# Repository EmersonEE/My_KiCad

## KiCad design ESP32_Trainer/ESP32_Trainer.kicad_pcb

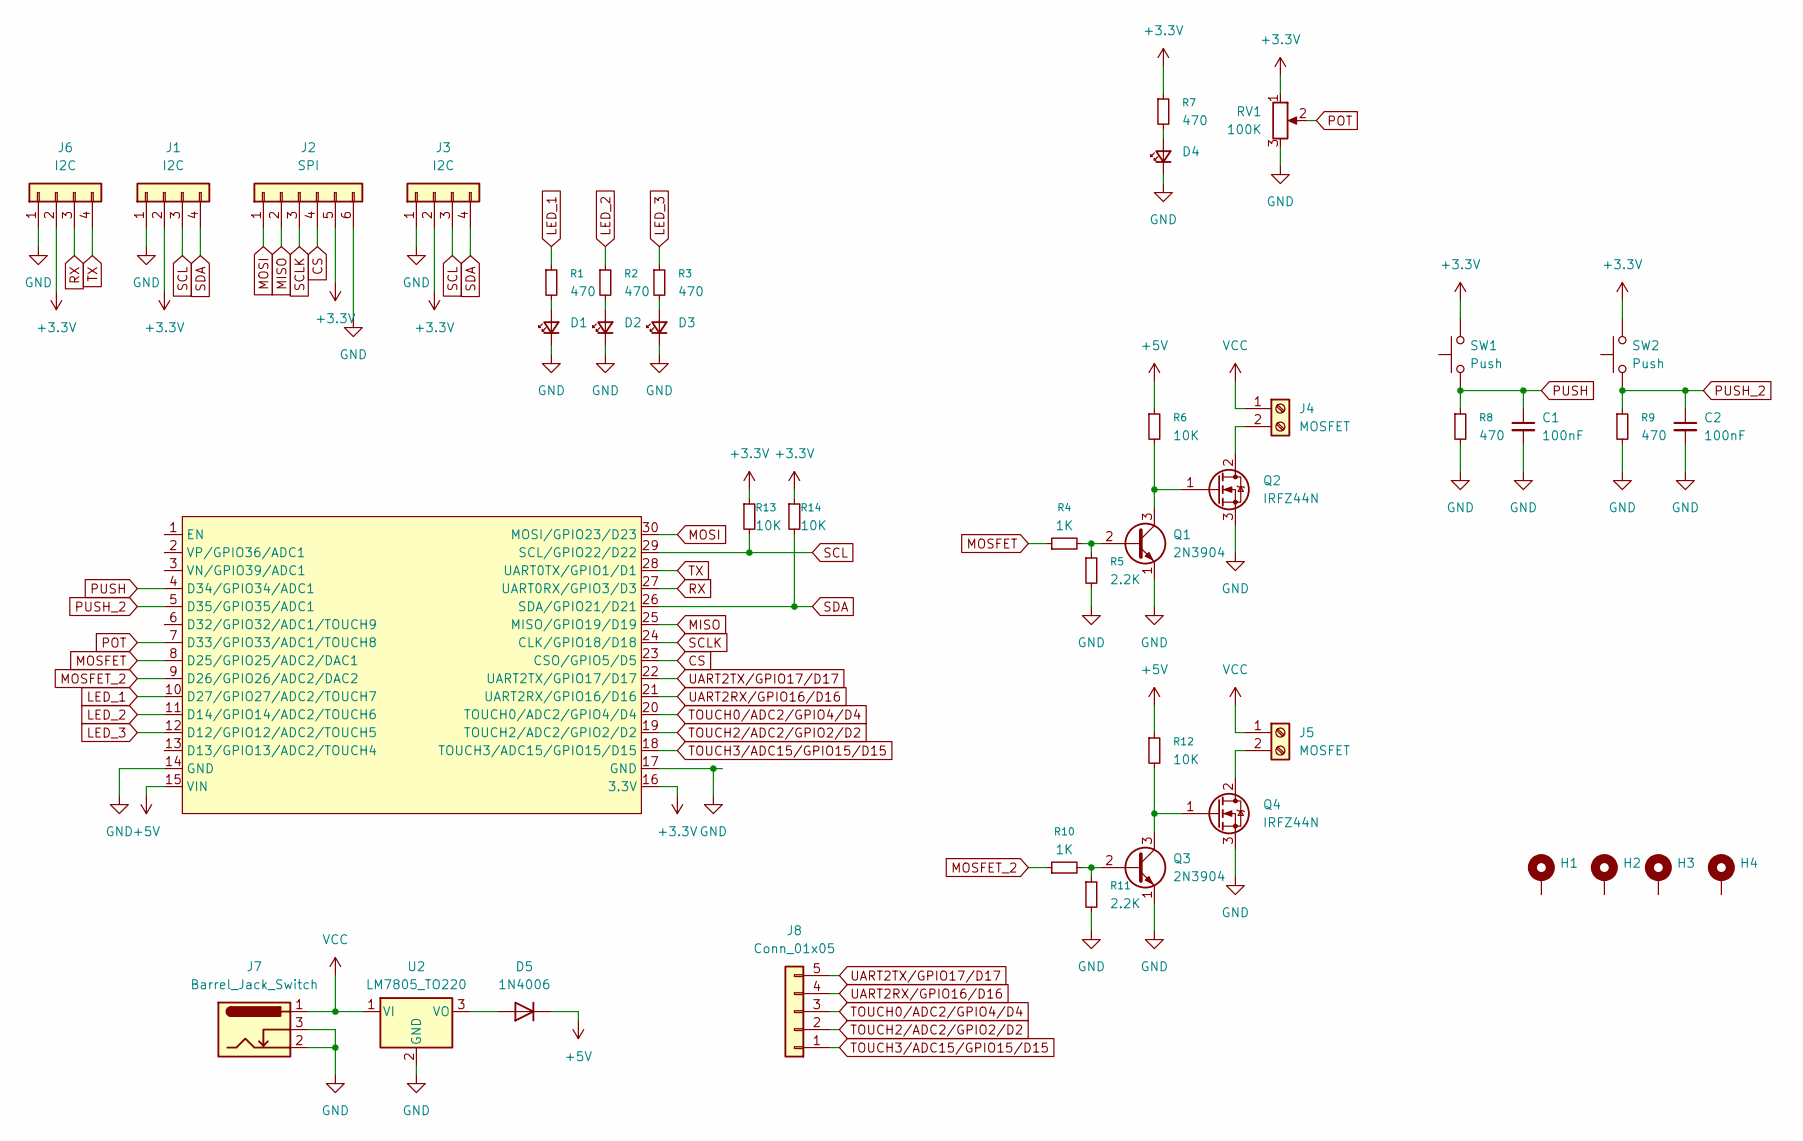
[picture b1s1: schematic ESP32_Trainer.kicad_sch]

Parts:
C1, C2: 100nF; C_Disc_D3.8mm_W2.6mm_P2.50mm
D1, D2, D3, D4: LED_D3.0mm
D5: 1N4006; D_DO-41_SOD81_P10.16mm_Horizontal
H1, H2, H3, H4: MountingHole_3.2mm_M3_Pad_Via
J1, J3, J6: I2C; PinHeader_1x04_P2.54mm_Vertical
J2: SPI; PinSocket_1x06_P2.54mm_Vertical
J4, J5: MOSFET; TerminalBlock_bornier-2_P5.08mm
J7: Barrel_Jack_Switch; BarrelJack_Horizontal
J8: Conn_01x05; PinHeader_1x05_P2.54mm_Vertical
Q1, Q3: 2N3904; TO-92L_Inline_Wide
Q2, Q4: IRFZ44N; TO-220-3_Vertical
R1, R2, R3, R7, R8, R9: 470; 1K
R4, R10: 1K
R5, R11: 2.2K; 1K
R6, R12, R13, R14: 10K; 1K
RV1: 100K; Potentiometer_Bourns_3296W_Vertical
SW1, SW2: Push; SW_PUSH_6mm
U1: ESP32_DevKit_V1_DOIT; ESP32_DEVKIT_V1_E32
U2: LM7805_TO220; TO-220-3_Horizontal_TabDown

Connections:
+3.3V: J1.2, J2.5, J3.2, J6.2, R7.1, R13.1, R14.1, RV1.1, SW1.2, SW2.2, U1.16 (3.3V)
+5V: D5.1 (K), R6.1, R12.1, U1.15 (VIN)
CS: J2.4, U1.23 (CSO/GPIO5/D5)
GND: C1.2, C2.2, D1.1 (K), D2.1 (K), D3.1 (K), D4.1 (K), J1.1, J2.6, J3.1, J6.1, J7.2, J7.3, Q1.1 (E), Q2.3 (S), Q3.1 (E), Q4.3 (S), R5.2, R8.2, R9.2, R11.2, RV1.3, U1.14 (GND), U1.17 (GND), U2.2 (GND)
LED_1: R1.1, U1.10 (D27/GPIO27/ADC2/TOUCH7)
LED_2: R2.1, U1.11 (D14/GPIO14/ADC2/TOUCH6)
LED_3: R3.1, U1.12 (D12/GPIO12/ADC2/TOUCH5)
MISO: J2.2, U1.25 (MISO/GPIO19/D19)
MOSFET: R4.1, U1.8 (D25/GPIO25/ADC2/DAC1)
MOSFET_2: R10.1, U1.9 (D26/GPIO26/ADC2/DAC2)
MOSI: J2.1, U1.30 (MOSI/GPIO23/D23)
unnamed: D1.2 (A), R1.2
unnamed: D2.2 (A), R2.2
unnamed: D3.2 (A), R3.2
unnamed: D4.2 (A), R7.2
unnamed: D5.2 (A), U2.3 (VO)
unnamed: J4.2, Q2.2 (D)
unnamed: J5.2, Q4.2 (D)
unnamed: Q1.2 (B), R4.2, R5.1
unnamed: Q1.3 (C), Q2.1 (G), R6.2
unnamed: Q3.2 (B), R10.2, R11.1
unnamed: Q3.3 (C), Q4.1 (G), R12.2
POT: RV1.2, U1.7 (D33/GPIO33/ADC1/TOUCH8)
PUSH: C1.1, R8.1, SW1.1, U1.4 (D34/GPIO34/ADC1)
PUSH_2: C2.1, R9.1, SW2.1, U1.5 (D35/GPIO35/ADC1)
RX: J6.3, U1.27 (UART0RX/GPIO3/D3)
SCL: J1.3, J3.3, R13.2, U1.29 (SCL/GPIO22/D22)
SCLK: J2.3, U1.24 (CLK/GPIO18/D18)
SDA: J1.4, J3.4, R14.2, U1.26 (SDA/GPIO21/D21)
TOUCH0/ADC2/GPIO4/D4: J8.3, U1.20 (TOUCH0/ADC2/GPIO4/D4)
TOUCH2/ADC2/GPIO2/D2: J8.2, U1.19 (TOUCH2/ADC2/GPIO2/D2)
TOUCH3/ADC15/GPIO15/D15: J8.1, U1.18 (TOUCH3/ADC15/GPIO15/D15)
TX: J6.4, U1.28 (UART0TX/GPIO1/D1)
UART2RX/GPIO16/D16: J8.4, U1.21 (UART2RX/GPIO16/D16)
UART2TX/GPIO17/D17: J8.5, U1.22 (UART2TX/GPIO17/D17)
VCC: J4.1, J5.1, J7.1, U2.1 (VI)

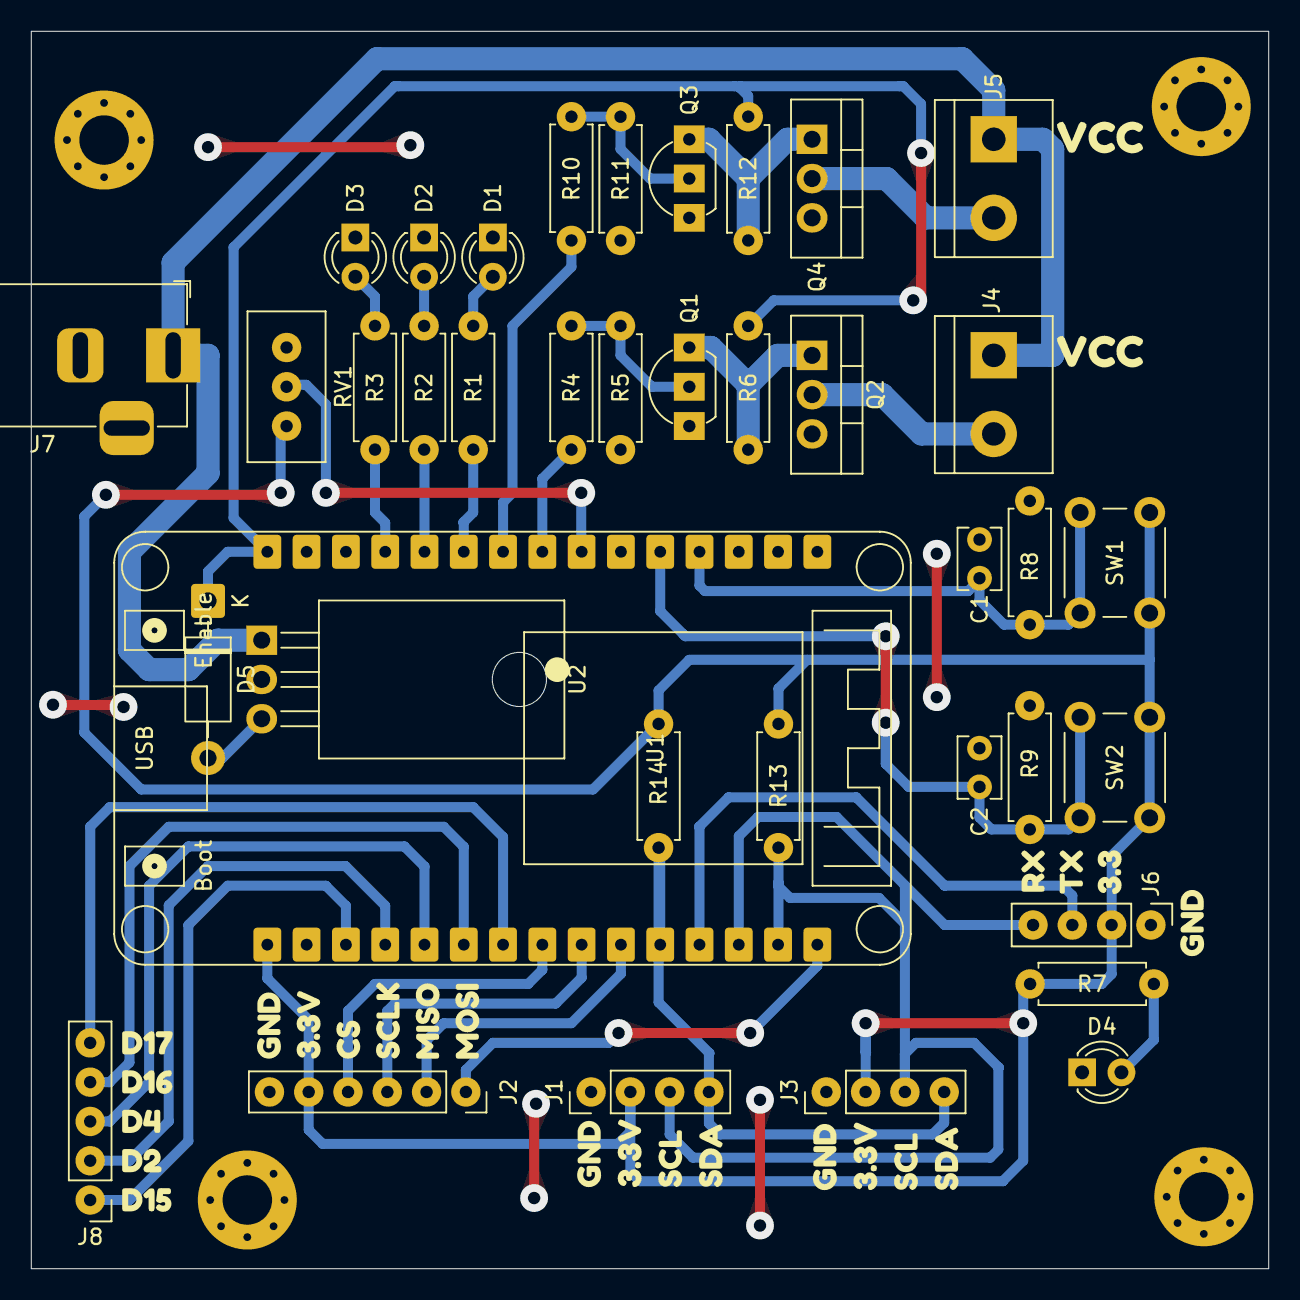
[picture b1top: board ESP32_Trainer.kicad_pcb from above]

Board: 2 copper layers, 80.0 x 80.0 mm, 67 parts (0 on the bottom side), 36 nets.

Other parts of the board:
kibuzzard-6849B4B1, kibuzzard-6849B4B1#2: G***; kibuzzard-6849B4B1
kibuzzard-6849B4BD, kibuzzard-6849B4BD#2: G***; kibuzzard-6849B4BD
kibuzzard-6849B4C9, kibuzzard-6849B4C9#2: G***; kibuzzard-6849B4C9
kibuzzard-6849B4D4, kibuzzard-6849B4D4#2: G***; kibuzzard-6849B4D4
kibuzzard-6849B34F: G***; kibuzzard-6849B34F
kibuzzard-6849B37B: G***; kibuzzard-6849B37B
kibuzzard-6849B38C: G***; kibuzzard-6849B38C
kibuzzard-6849B41C: G***; kibuzzard-6849B41C
kibuzzard-6849B45E: G***; kibuzzard-6849B45E
kibuzzard-6849B51A: G***; kibuzzard-6849B51A
kibuzzard-6849B53A: G***; kibuzzard-6849B53A
kibuzzard-6849B320: G***; kibuzzard-6849B320
kibuzzard-6849B368: G***; kibuzzard-6849B368
kibuzzard-6849B393: G***; kibuzzard-6849B393
kibuzzard-6849B428: G***; kibuzzard-6849B428
kibuzzard-6849B446: G***; kibuzzard-6849B446
kibuzzard-6849B454: G***; kibuzzard-6849B454
kibuzzard-6849B511: G***; kibuzzard-6849B511
kibuzzard-6849B541: G***; kibuzzard-6849B541
kibuzzard-6849B815, kibuzzard-6849B815#2: G***; kibuzzard-6849B815

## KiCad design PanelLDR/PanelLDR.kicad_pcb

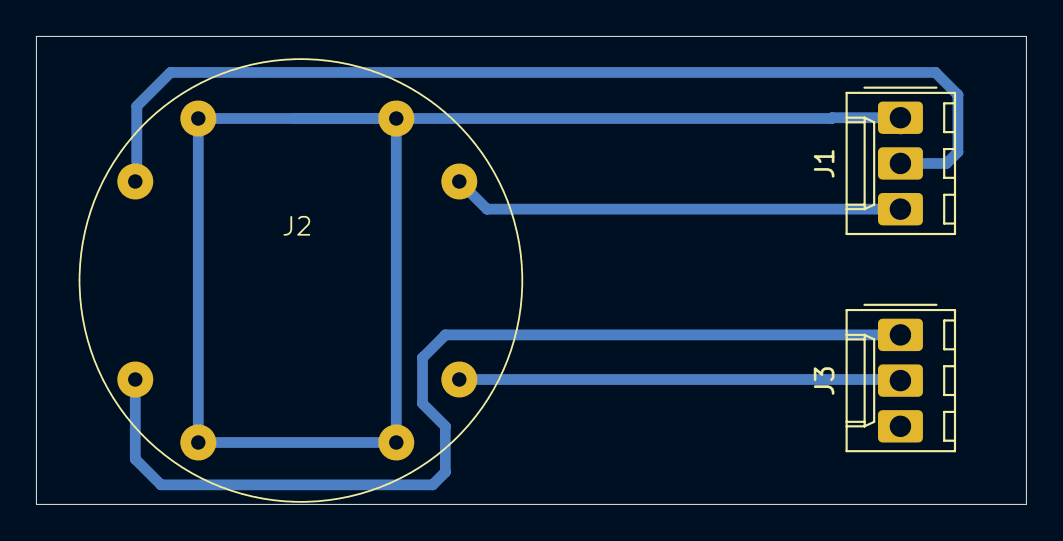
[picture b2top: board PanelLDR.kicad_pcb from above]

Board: 2 copper layers, 55.0 x 26.0 mm, 3 parts (0 on the bottom side), 5 nets.

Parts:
J1, J3: Conn_01x03; Molex_KK-254_AE-6410-03A_1x03_P2.54mm_Vertical
J2: Conn_01x08; LDR_PANEL

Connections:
+3.3V: J1.1, J2.2, J2.3, J2.6, J2.7
LDR_ID: J2.4, J3.2
LDR_II: J2.1, J3.1
LDR_SD: J1.3, J2.5
LDR_SI: J1.2, J2.8

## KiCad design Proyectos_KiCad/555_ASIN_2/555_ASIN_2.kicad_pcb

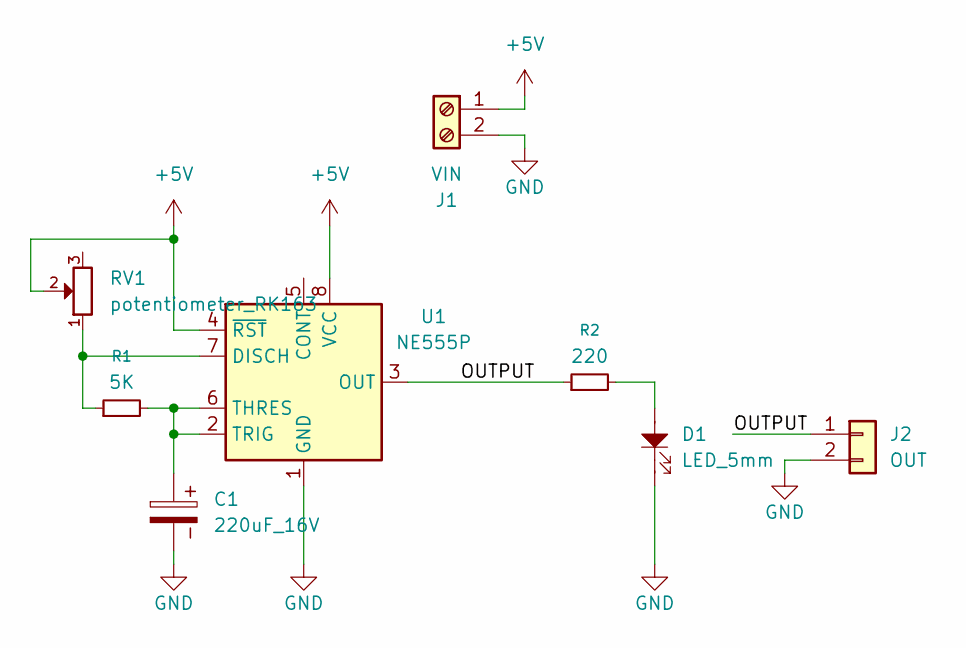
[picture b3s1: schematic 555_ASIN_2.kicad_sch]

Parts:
C1: 220uF_16V; CP_Radial_D8.0mm_P3.50mm
D1: LED_5mm; LED_D5.0mm
J1: VIN; TerminalBlock_Phoenix_MKDS-1,5-2-5.08_1x02_P5.08mm_Horizont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
J2: OUT; PinHeader_1x02_P2.54mm_Vertical
R1: 5K; 5.1K
R2: 220
RV1: potentiometer_RK163; Potentiometer_Alps_RK163_Single_Horizontal
U1: NE555P; DIP-8_W7.62mm_LongPads

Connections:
+5V: J1.1, RV1.2, U1.4 (~RST), U1.8 (VCC)
/OUTPUT: J2.1, R2.1, U1.3 (OUT)
GND: C1.2, D1.1, J1.2, J2.2, U1.1 (GND)
unnamed: D1.2, R2.2
unnamed: R1.1, RV1.1, U1.7 (DISCH)
unnamed: C1.1, R1.2, U1.2 (TRIG), U1.6 (THRES)

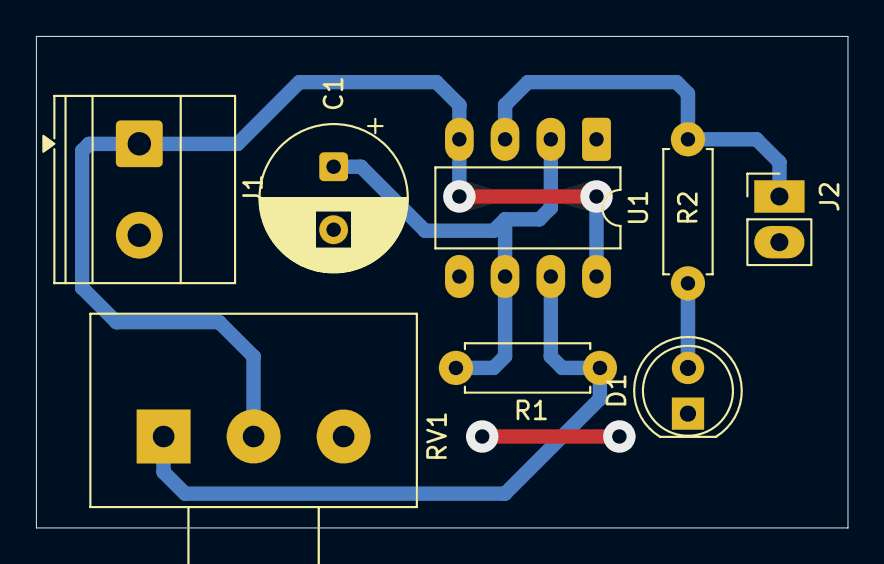
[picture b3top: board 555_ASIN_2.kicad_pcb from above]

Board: 2 copper layers, 45.1 x 27.3 mm, 8 parts (0 on the bottom side), 6 nets.

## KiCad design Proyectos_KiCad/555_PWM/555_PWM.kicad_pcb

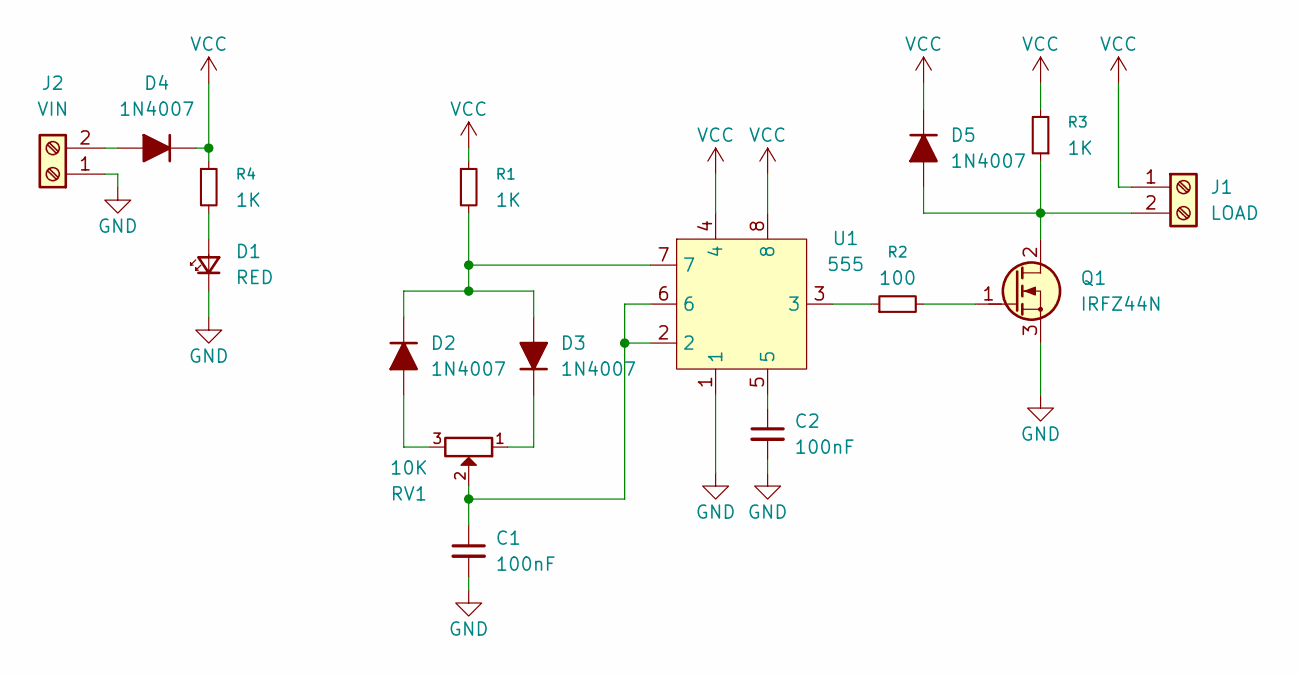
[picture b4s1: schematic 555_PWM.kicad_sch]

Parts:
C1, C2: 100nF; C_Disc_D3.8mm_W2.6mm_P2.50mm
D1: RED; LED_D5.0mm
D2, D3, D4: 1N4007; D_DO-41_SOD81_P7.62mm_Horizontal
D5: 1N4007; D_DO-41_SOD81_P10.16mm_Horizontal
J1: LOAD; TerminalBlock_Phoenix_MKDS-1,5-2-5.08_1x02_P5.08mm_Horizont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
J2: VIN; TerminalBlock_Phoenix_MKDS-1,5-2-5.08_1x02_P5.08mm_Horizont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
Q1: IRFZ44N; TO-220-3_Vertical_GDS
R1, R3, R4: 1K
R2: 100
RV1: 10K; Potentiometer_Alps_RK163_Single_Horizontal
U1: 555; DIP-8_W7.62mm_LongPads

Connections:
GND: C1.2, C2.2, D1.1 (K), J2.1, Q1.3 (S), U1.1
unnamed: C1.1, RV1.2, U1.2, U1.6
unnamed: C2.1, U1.5
unnamed: D1.2 (A), R4.2
unnamed: D2.2 (A), RV1.3
unnamed: D2.1 (K), D3.2 (A), R1.2, U1.7
unnamed: D3.1 (K), RV1.1
unnamed: D4.2 (A), J2.2
unnamed: D5.2 (A), J1.2, Q1.2 (D), R3.1
unnamed: Q1.1 (G), R2.2
unnamed: R2.1, U1.3
VCC: D4.1 (K), D5.1 (K), J1.1, R1.1, R3.2, R4.1, U1.4, U1.8

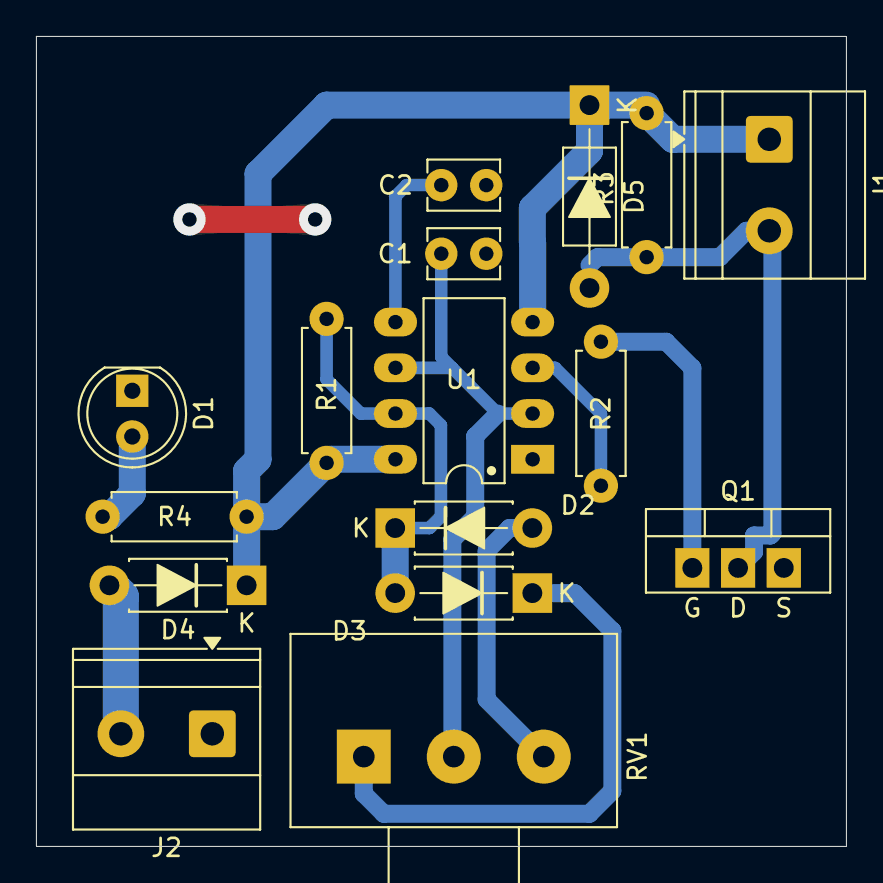
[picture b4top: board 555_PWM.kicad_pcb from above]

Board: 2 copper layers, 45.0 x 45.0 mm, 16 parts (0 on the bottom side), 12 nets.

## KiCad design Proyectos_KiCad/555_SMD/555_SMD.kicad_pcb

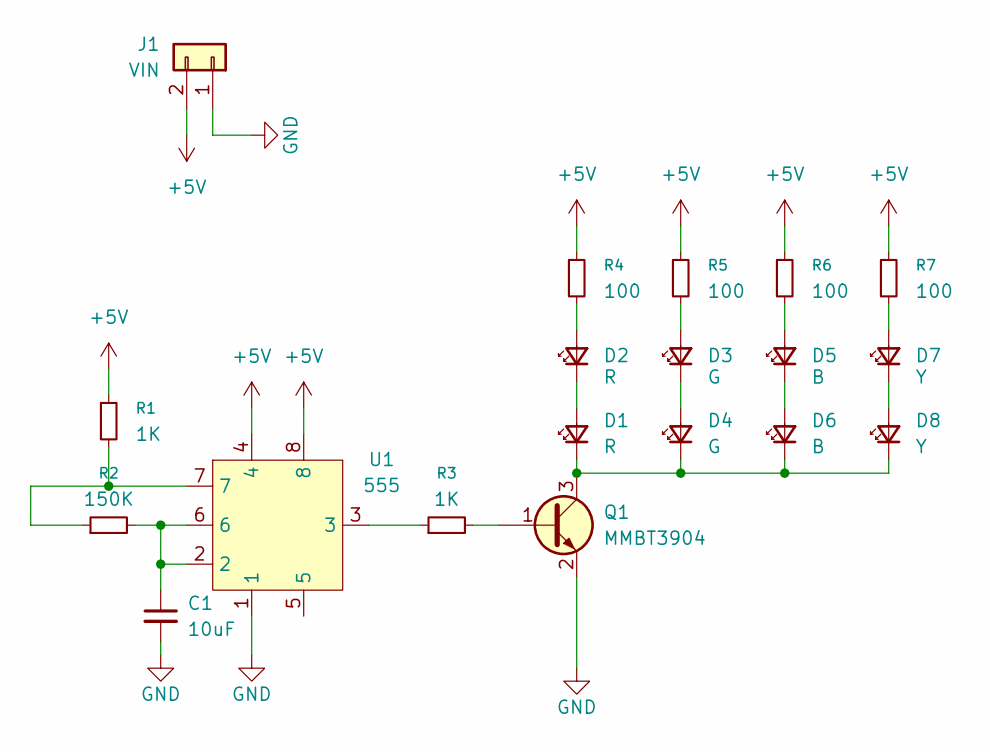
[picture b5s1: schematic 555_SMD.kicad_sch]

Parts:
C1: 10uF; C_0805_2012Metric_Pad1.18x1.45mm
D1, D2: R; LED_0805_2012Metric_Pad1.15x1.40mm_HandSolder
D3, D4: G; LED_1206_3216Metric_Pad1.42x1.75mm
D5, D6: B; LED_0805_2012Metric_Pad1.15x1.40mm_HandSolder
D7, D8: Y; LED_1206_3216Metric_Pad1.42x1.75mm
J1: VIN; PinHeader_1x02_P2.54mm_Horizontal
Q1: MMBT3904; SOT-23
R1, R3: 1K; R_0805_2012Metric_Pad1.20x1.40mm_HandSolder
R2: 150K; R_0805_2012Metric_Pad1.20x1.40mm_HandSolder
R4, R5, R6, R7: 100; R_0805_2012Metric_Pad1.20x1.40mm_HandSolder
U1: 555; SO-8_3.9x4.9mm_P1.27mm

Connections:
+5V: J1.2, R1.1, R4.1, R5.1, R6.1, R7.1, U1.4, U1.8
GND: C1.2, J1.1, Q1.2 (E), U1.1
unnamed: C1.1, R2.2, U1.2, U1.6
unnamed: D1.2 (A), D2.1 (K)
unnamed: D1.1 (K), D4.1 (K), D6.1 (K), D8.1 (K), Q1.3 (C)
unnamed: D2.2 (A), R4.2
unnamed: D3.2 (A), R5.2
unnamed: D3.1 (K), D4.2 (A)
unnamed: D5.2 (A), R6.2
unnamed: D5.1 (K), D6.2 (A)
unnamed: D7.2 (A), R7.2
unnamed: D7.1 (K), D8.2 (A)
unnamed: Q1.1 (B), R3.2
unnamed: R1.2, R2.1, U1.7
unnamed: R3.1, U1.3

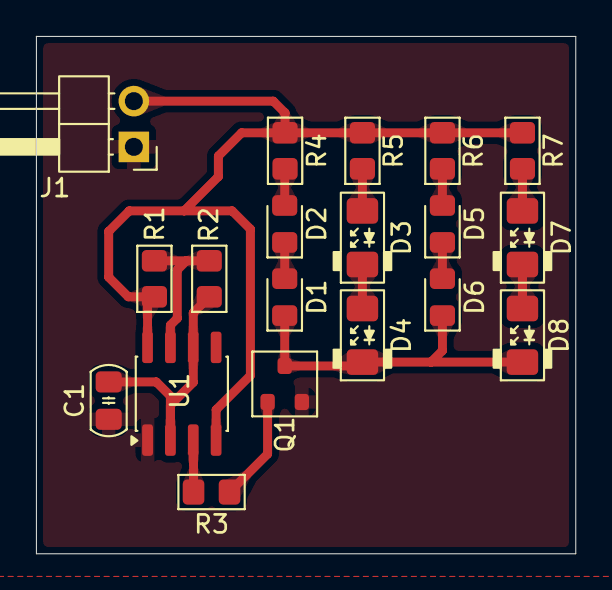
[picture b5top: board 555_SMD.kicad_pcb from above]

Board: 2 copper layers, 30.0 x 28.7 mm, 19 parts (0 on the bottom side), 15 nets.

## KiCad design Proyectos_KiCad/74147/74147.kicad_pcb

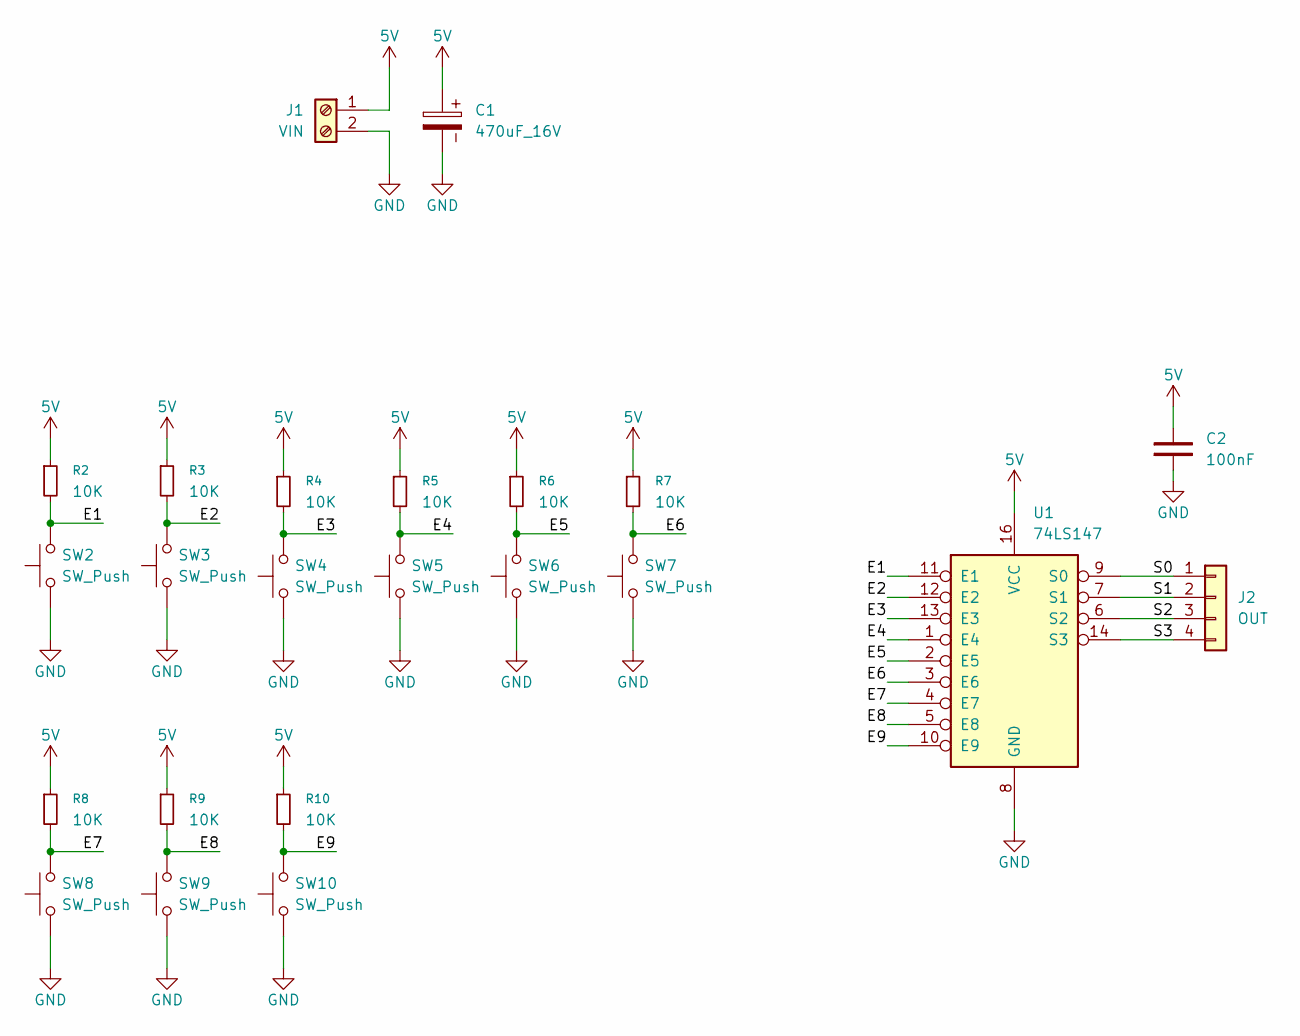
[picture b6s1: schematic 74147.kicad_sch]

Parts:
C1: 470uF_16V; CP_Radial_D8.0mm_P3.50mm
C2: 100nF; C_Disc_D5.0mm_W2.5mm_P2.50mm
J1: VIN; TerminalBlock_Phoenix_MKDS-1,5-2-5.08_1x02_P5.08mm_Horizont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
J2: OUT; PinHeader_1x04_P2.54mm_Vertical
R2, R3, R4, R5, R6, R7, R8, R9, R10: 10K
SW2, SW3, SW4, SW5, SW6, SW7, SW8, SW9, SW10: SW_Push; SW_PUSH_6mm
U1: 74LS147; DIP-16_W7.62mm_LongPads

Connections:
5V: C1.1, C2.2, J1.1, R2.1, R3.1, R4.1, R5.1, R6.1, R7.1, R8.1, R9.1, R10.1, U1.16 (VCC)
/E1: R2.2, SW2.2, U1.11 (E1)
/E2: R3.2, SW3.2, U1.12 (E2)
/E3: R4.2, SW4.2, U1.13 (E3)
/E4: R5.2, SW5.2, U1.1 (E4)
/E5: R6.2, SW6.2, U1.2 (E5)
/E6: R7.2, SW7.2, U1.3 (E6)
/E7: R8.2, SW8.2, U1.4 (E7)
/E8: R9.2, SW9.2, U1.5 (E8)
/E9: R10.2, SW10.2, U1.10 (E9)
/S0: J2.1, U1.9 (S0)
/S1: J2.2, U1.7 (S1)
/S2: J2.3, U1.6 (S2)
/S3: J2.4, U1.14 (S3)
GND: C1.2, C2.1, J1.2, SW2.1, SW3.1, SW4.1, SW5.1, SW6.1, SW7.1, SW8.1, SW9.1, SW10.1, U1.8 (GND)

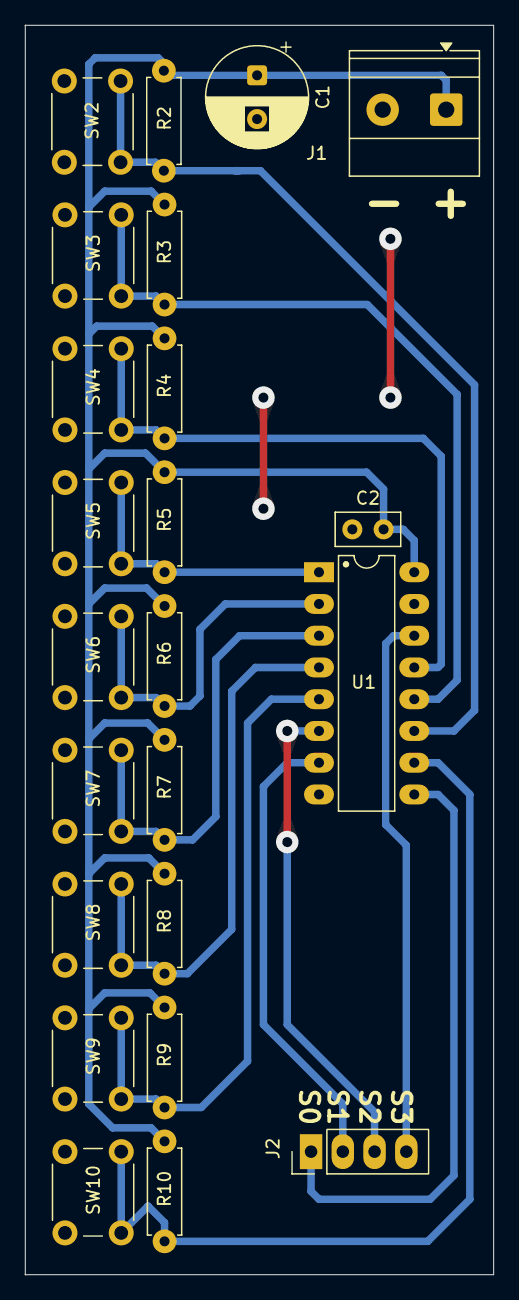
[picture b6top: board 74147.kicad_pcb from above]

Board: 2 copper layers, 37.5 x 99.9 mm, 23 parts (0 on the bottom side), 15 nets.

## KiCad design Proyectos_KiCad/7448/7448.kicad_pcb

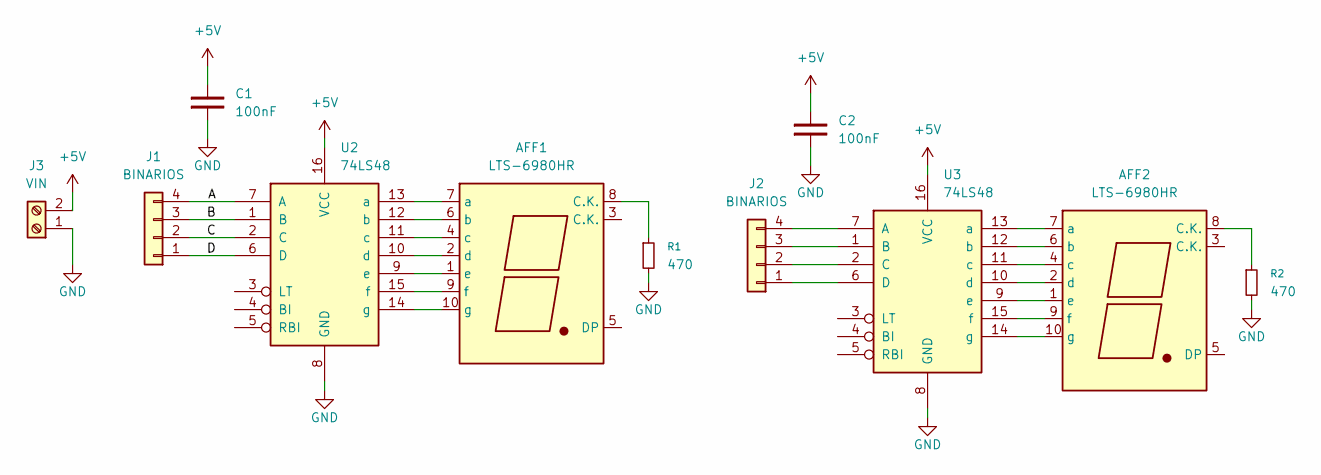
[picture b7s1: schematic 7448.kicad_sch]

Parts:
AFF1, AFF2: LTS-6980HR; 7SegmentLED_LTS6760_LTS6780
C1, C2: 100nF; C_Disc_D5.0mm_W2.5mm_P2.50mm
J1, J2: BINARIOS; PinHeader_1x04_P2.54mm_Vertical
J3: VIN; TerminalBlock_Phoenix_MKDS-1,5-2-5.08_1x02_P5.08mm_Horizont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
R1, R2: 470
U2, U3: 74LS48; DIP-16_W7.62mm_LongPads

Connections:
+5V: C1.2, C2.2, J3.2, U2.16 (VCC), U3.16 (VCC)
/A: J1.4, U2.7 (A)
/B: J1.3, U2.1 (B)
/C: J1.2, U2.2 (C)
/D: J1.1, U2.6 (D)
GND: C1.1, C2.1, J3.1, R1.2, R2.2, U2.8 (GND), U3.8 (GND)
unnamed: AFF1.8 (C.K.), R1.1
unnamed: AFF1.7 (a), U2.13 (a)
unnamed: AFF1.6 (b), U2.12 (b)
unnamed: AFF1.4 (c), U2.11 (c)
unnamed: AFF1.2 (d), U2.10 (d)
unnamed: AFF1.1 (e), U2.9 (e)
unnamed: AFF1.9 (f), U2.15 (f)
unnamed: AFF1.10 (g), U2.14 (g)
unnamed: AFF2.8 (C.K.), R2.1
unnamed: AFF2.7 (a), U3.13 (a)
unnamed: AFF2.6 (b), U3.12 (b)
unnamed: AFF2.4 (c), U3.11 (c)
unnamed: AFF2.2 (d), U3.10 (d)
unnamed: AFF2.1 (e), U3.9 (e)
unnamed: AFF2.9 (f), U3.15 (f)
unnamed: AFF2.10 (g), U3.14 (g)
unnamed: J2.1, U3.6 (D)
unnamed: J2.2, U3.2 (C)
unnamed: J2.3, U3.1 (B)
unnamed: J2.4, U3.7 (A)

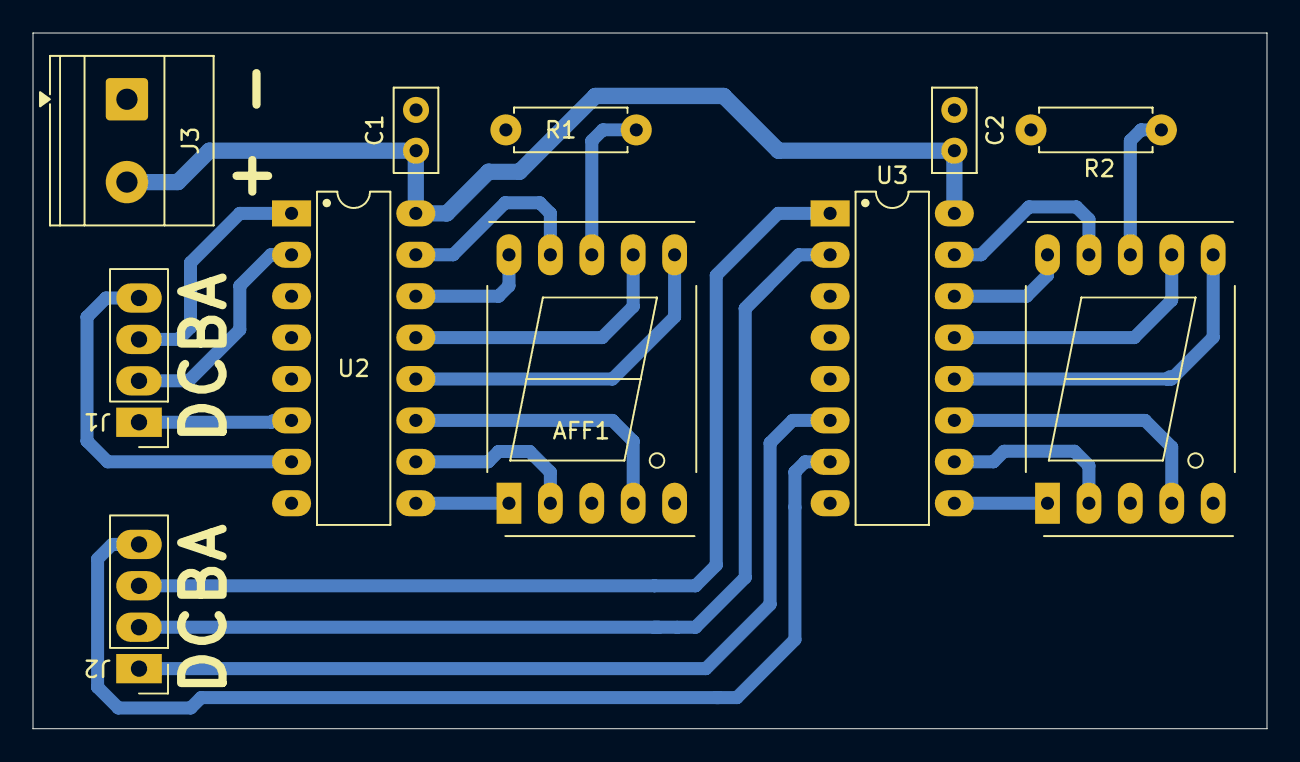
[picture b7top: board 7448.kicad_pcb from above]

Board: 2 copper layers, 75.7 x 42.7 mm, 11 parts (0 on the bottom side), 26 nets.

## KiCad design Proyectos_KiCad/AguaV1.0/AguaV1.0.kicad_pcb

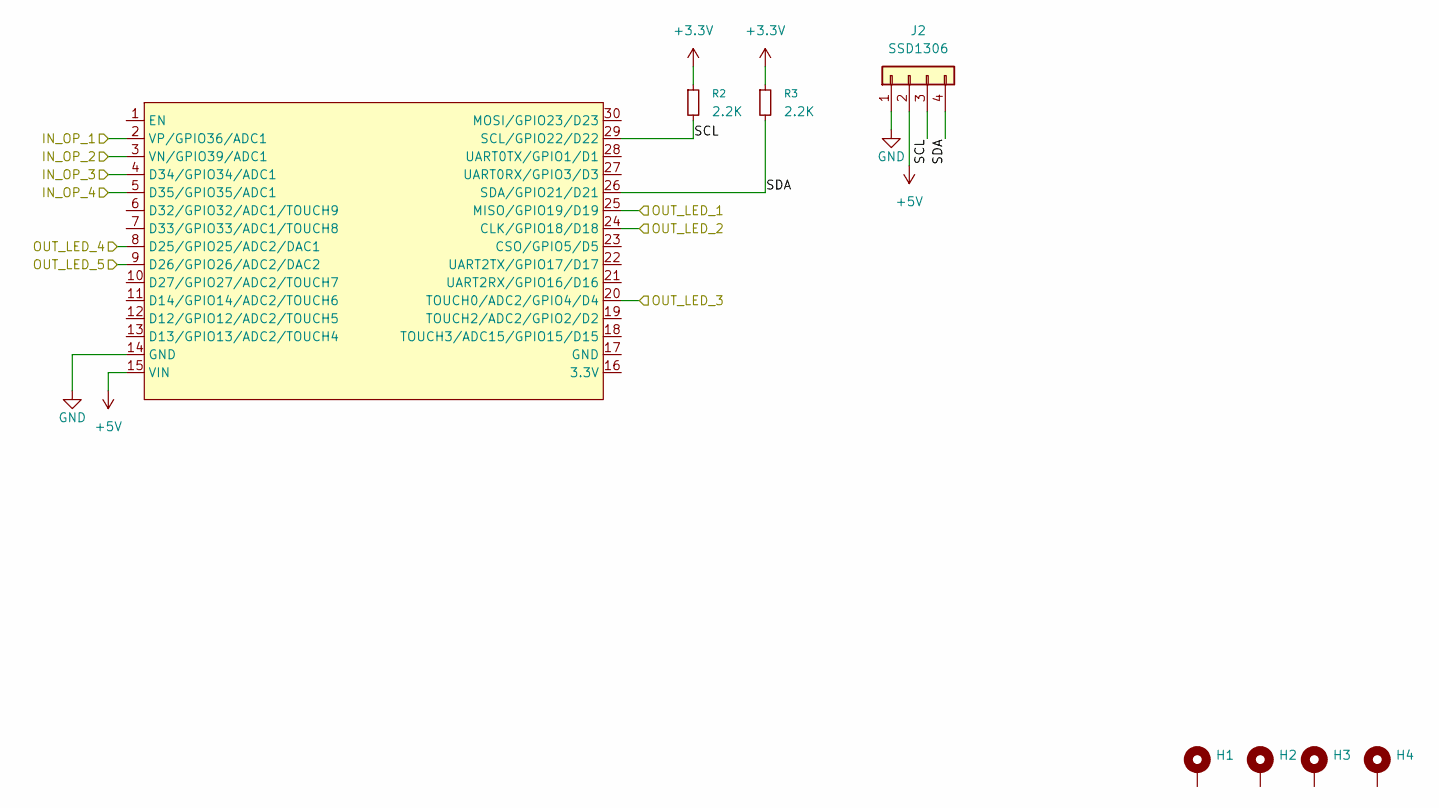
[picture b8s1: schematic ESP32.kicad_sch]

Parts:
H1, H2, H3, H4: MountingHole_3.2mm_M3_Pad_Via
J2: SSD1306; Molex_KK-254_AE-6410-04A_1x04_P2.54mm_Vertical
R2, R3: 2.2K
U1: ESP32_DevKit_V1_DOIT; ESP32_DEVKIT_V1_E32

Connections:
+3.3V: R2.1, R3.1; also elsewhere on the board
+5V: J2.2, U1.15 (VIN); also elsewhere on the board
/ESP32/IN_OP_1: U1.2 (VP/GPIO36/ADC1); also elsewhere on the board
/ESP32/IN_OP_2: U1.3 (VN/GPIO39/ADC1); also elsewhere on the board
/ESP32/IN_OP_3: U1.4 (D34/GPIO34/ADC1); also elsewhere on the board
/ESP32/IN_OP_4: U1.5 (D35/GPIO35/ADC1); also elsewhere on the board
/ESP32/OUT_LED_1: U1.25 (MISO/GPIO19/D19); also elsewhere on the board
/ESP32/OUT_LED_2: U1.24 (CLK/GPIO18/D18); also elsewhere on the board
/ESP32/OUT_LED_3: U1.20 (TOUCH0/ADC2/GPIO4/D4); also elsewhere on the board
/ESP32/OUT_LED_4: U1.8 (D25/GPIO25/ADC2/DAC1); also elsewhere on the board
/ESP32/OUT_LED_5: U1.9 (D26/GPIO26/ADC2/DAC2); also elsewhere on the board
/ESP32/SCL: J2.3, R2.2, U1.29 (SCL/GPIO22/D22)
/ESP32/SDA: J2.4, R3.2, U1.26 (SDA/GPIO21/D21)
GND: J2.1, U1.14 (GND); also elsewhere on the board

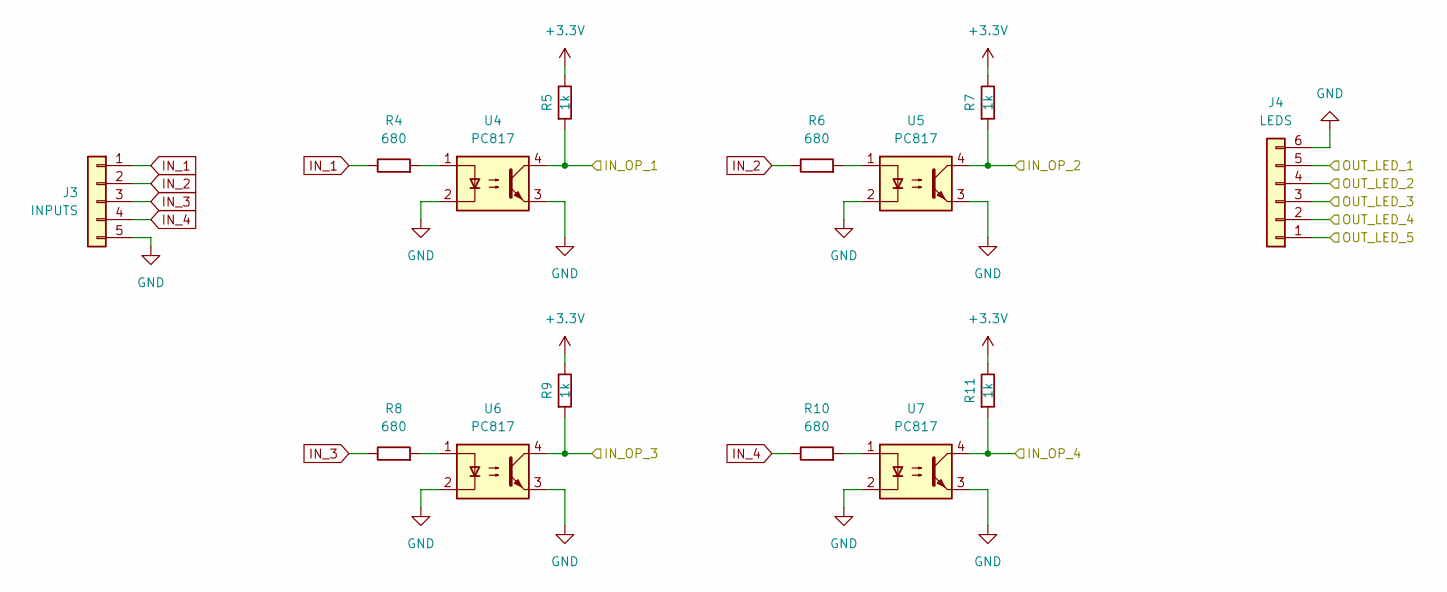
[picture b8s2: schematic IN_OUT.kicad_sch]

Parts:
J3: INPUTS; PinHeader_1x05_P2.54mm_Vertical
J4: LEDS; PinHeader_1x06_P2.54mm_Vertical
R4, R6, R8, R10: 680; 2.2K
R5, R7, R9, R11: 1k; 1K
U4, U5, U6, U7: PC817; DIP-4_W7.62mm

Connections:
+3.3V: R5.2, R7.2, R9.2, R11.2; also elsewhere on the board
/ESP32/IN_OP_1: R5.1, U4.4; also elsewhere on the board
/ESP32/IN_OP_2: R7.1, U5.4; also elsewhere on the board
/ESP32/IN_OP_3: R9.1, U6.4; also elsewhere on the board
/ESP32/IN_OP_4: R11.1, U7.4; also elsewhere on the board
/ESP32/OUT_LED_1: J4.5; also elsewhere on the board
/ESP32/OUT_LED_2: J4.4; also elsewhere on the board
/ESP32/OUT_LED_3: J4.3; also elsewhere on the board
/ESP32/OUT_LED_4: J4.2; also elsewhere on the board
/ESP32/OUT_LED_5: J4.1; also elsewhere on the board
GND: J3.5, J4.6, U4.2, U4.3, U5.2, U5.3, U6.2, U6.3, U7.2, U7.3; also elsewhere on the board
IN_1: J3.1, R4.2
IN_2: J3.2, R6.2
IN_3: J3.3, R8.2
IN_4: J3.4, R10.2
unnamed: R4.1, U4.1
unnamed: R6.1, U5.1
unnamed: R8.1, U6.1
unnamed: R10.1, U7.1

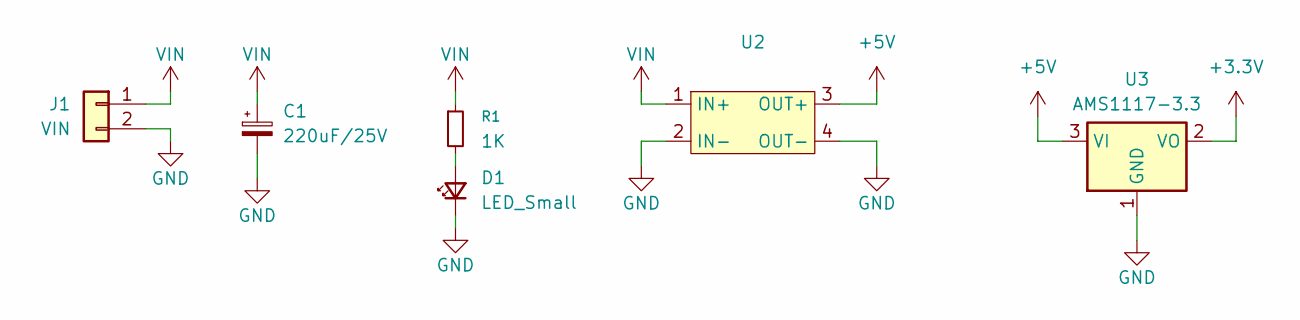
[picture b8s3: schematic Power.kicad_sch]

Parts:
C1: 220uF/25V; CP_Radial_D8.0mm_P3.50mm
D1: LED_Small; LED_D5.0mm
J1: VIN; TerminalBlock_Phoenix_MKDS-1,5-2-5.08_1x02_P5.08mm_Horizont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
R1: 1K
U2: LM2596S
U3: AMS1117-3.3; SOT-223-3_TabPin2

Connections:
+3.3V: U3.2 (VO); also elsewhere on the board
+5V: U2.3 (OUT+), U3.3 (VI); also elsewhere on the board
GND: C1.2, D1.1 (K), J1.2, U2.2 (IN-), U2.4 (OUT-), U3.1 (GND); also elsewhere on the board
unnamed: D1.2 (A), R1.2
VIN: C1.1, J1.1, R1.1, U2.1 (IN+)
